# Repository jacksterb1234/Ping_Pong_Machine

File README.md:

# Ping Pong Machine — Table Tennis Serving Robot

A fully custom table tennis serving robot designed for serve-receive practice. Features dual-axis spin control (pitch and yaw), a printed spindexer, and a Bluetooth mobile app for wireless control. Powered entirely from a single USB-C connection.

## Features

- **Dual-axis spin control** — independent pitch and yaw adjustment for realistic serve variation
- **Printed spindexer** — feeds and spins balls for consistent delivery
- **Bluetooth control** via a custom mobile app (Expo/React Native) for easy wireless operation
- **USB-C powered** — single cable for full system power
- **Modular electronics design:**
  - USB-C PD power negotiation board
  - Motor and microcontroller breakout board
  - Buck voltage regulation board
- Designed and fabricated with **JLCPCB** for PCB production

## Repository Structure

```
Ping_Pong_Machine/
├── Kicad/               # KiCad PCB projects (power, motor breakout, buck reg)
├── Code/                # Microcontroller firmware and Bluetooth app code
├── CAD/                 # 3D-printable parts (spindexer, frame, wheels)
├── Sims/                # Simulations for board fit and assembly
└── ul_PTPS543021DRLR/   # Custom KiCad footprint
```

## Electronics

| Board | Function |
|-------|----------|
| USB-C PD board | Negotiates input voltage from USB-C PD source |
| Motor breakout | Drives launch and spin motors |
| MCU breakout | Hosts microcontroller and Bluetooth module |
| Buck regulator | Steps down voltage for logic-level components |

## Mobile App

Controlled via a custom **React Native (Expo)** app that connects over Bluetooth. The app allows users to adjust spin type, speed, and frequency from their phone—no physical controls on the machine required.

## Tools Used

- **KiCad** — PCB schematic and layout
- **JLCPCB** — PCB fabrication and SMT assembly
- **Fusion360 / SolidWorks** — Mechanical CAD (frame and launcher)
- **Expo (React Native)** — Mobile app development

## Author

**Jackson Barber** — [github.com/jacksterb1234](https://github.com/jacksterb1234)

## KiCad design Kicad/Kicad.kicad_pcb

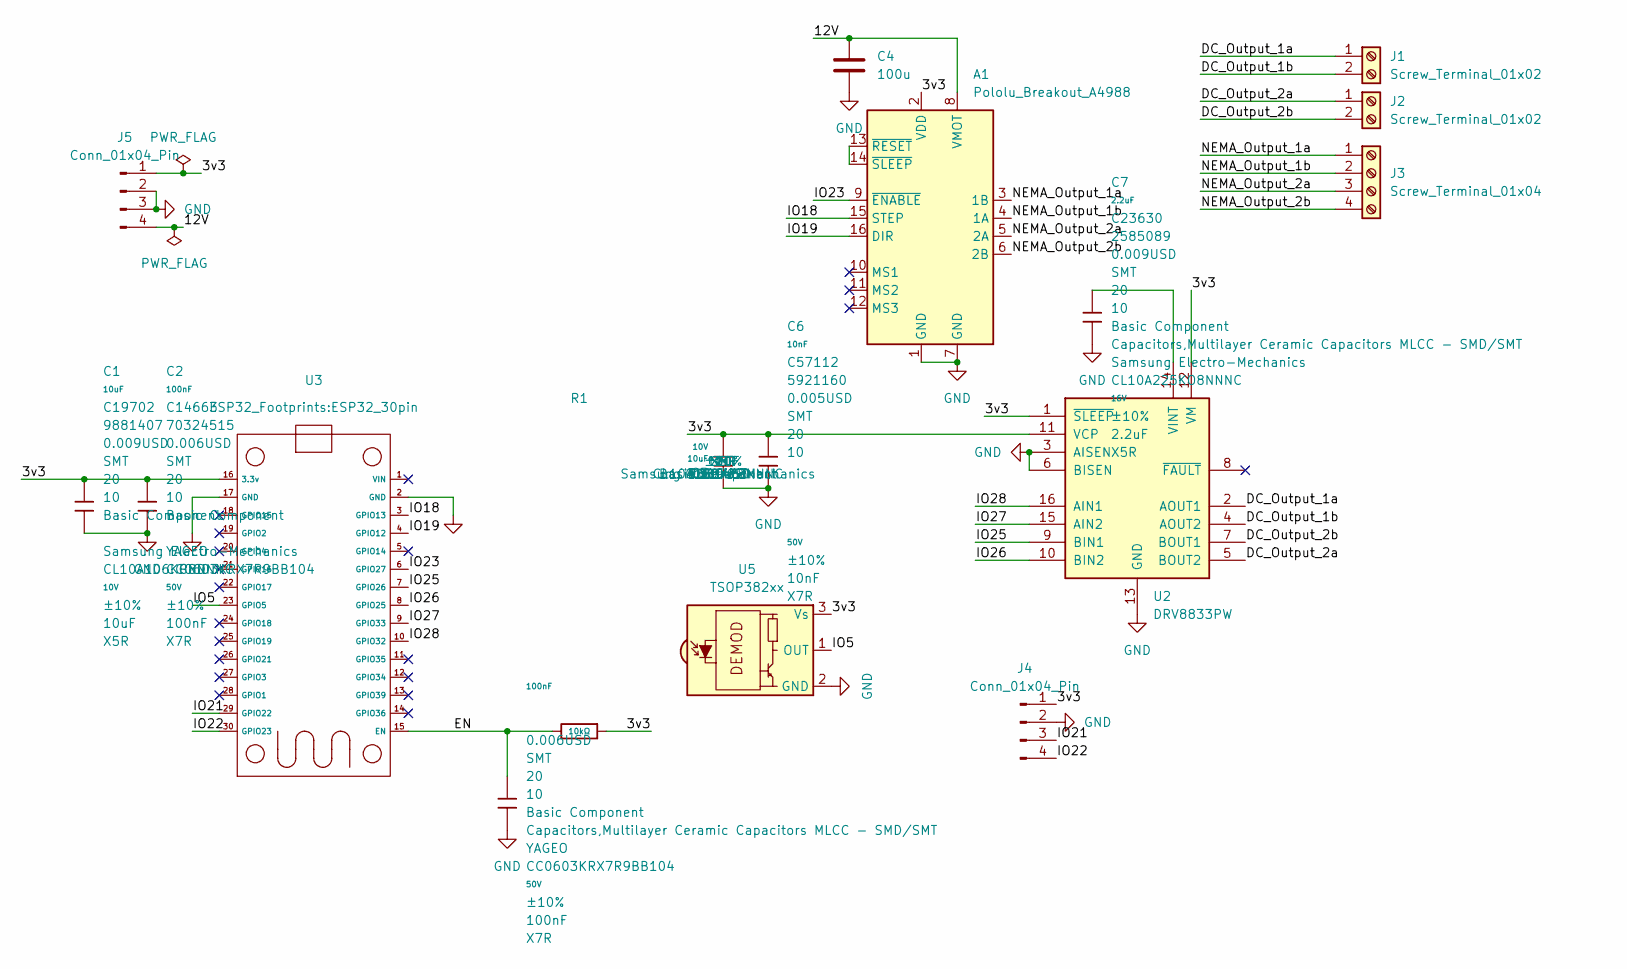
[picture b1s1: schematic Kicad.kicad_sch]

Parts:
A1: Pololu_Breakout_A4988; Pololu_Breakout-16_15.2x20.3mm
C1, C5: 10uF; C_0805_2012Metric_Pad1.18x1.45mm_HandSolder; Voltage Rated 10V; Tolerance ±10%; Part CL10A106KP8NNNC; LCSC C19702
C2, C3: 100nF; C_0805_2012Metric_Pad1.18x1.45mm_HandSolder; Voltage Rated 50V; Tolerance ±10%; Part CC0603KRX7R9BB104; LCSC C14663
C4: 100u; C_Radial_D8.0mm_H11.5mm_P3.50mm
C6: 10nF; C_0805_2012Metric_Pad1.18x1.45mm_HandSolder; Voltage Rated 50V; Tolerance ±10%; Part 0603B103K500NT; LCSC C57112
C7: 2.2uF; C_0805_2012Metric_Pad1.18x1.45mm_HandSolder; Voltage Rated 16V; Tolerance ±10%; Part CL10A225KO8NNNC; LCSC C23630
J1, J2: Screw_Terminal_01x02; TerminalBlock_RND_205-00045_1x02_P5.00mm_Horizontal
J3: Screw_Terminal_01x04; TerminalBlock_RND_205-00003_1x04_P5.00mm_Horizontal
J4, J5: Conn_01x04_Pin; PinHeader_1x04_P2.54mm_Vertical
R1: 10kΩ; R_0805_2012Metric_Pad1.20x1.40mm_HandSolder; Overload Voltage (Max) 75V; Tolerance ±1%; Part 0603WAF1002T5E; LCSC C25804
U2: DRV8833PW; TSSOP-16_4.4x5mm_P0.65mm
U3: ESP32_30pin
U5: TSOP382xx; Vishay_MINICAST-3Pin

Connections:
/3v3: A1.2 (VDD), C1.2, C2.2, C5.2, C6.2, J4.1, J5.1, R1.1, U2.1 (~SLEEP), U2.11 (VCP), U2.12 (VM), U3.16 (3.3v), U5.3 (Vs)
/12V: A1.8 (VMOT), C4.2, J5.4
/DC_Output_1a: J1.1, U2.2 (AOUT1)
/DC_Output_1b: J1.2, U2.4 (AOUT2)
/DC_Output_2a: J2.1, U2.5 (BOUT2)
/DC_Output_2b: J2.2, U2.7 (BOUT1)
/EN: C3.1, R1.2, U3.15 (EN)
/IO5: U3.23 (GPIO5), U5.1 (OUT)
/IO18: A1.15 (STEP), U3.3 (GPIO13)
/IO19: A1.16 (DIR), U3.4 (GPIO12)
/IO21: J4.3, U3.29 (GPIO22)
/IO22: J4.4, U3.30 (GPIO23)
/IO23: A1.9 (~ENABLE), U3.6 (GPIO27)
/IO25: U2.9 (BIN1), U3.7 (GPIO26)
/IO26: U2.10 (BIN2), U3.8 (GPIO25)
/IO27: U2.15 (AIN2), U3.9 (GPIO33)
/IO28: U2.16 (AIN1), U3.10 (GPIO32)
/NEMA_Output_1a: A1.3 (1B), J3.1
/NEMA_Output_1b: A1.4 (1A), J3.2
/NEMA_Output_2a: A1.5 (2A), J3.3
/NEMA_Output_2b: A1.6 (2B), J3.4
GND: A1.1 (GND), A1.7 (GND), C1.1, C2.1, C3.2, C4.1, C5.1, C6.1, C7.1, J4.2, J5.2, J5.3, U2.3 (AISEN), U2.6 (BISEN), U2.13 (GND), U3.2 (GND), U3.17 (GND), U5.2 (GND)
unnamed: A1.13 (~RESET), A1.14 (~SLEEP)
unnamed: C7.2, U2.14 (VINT)

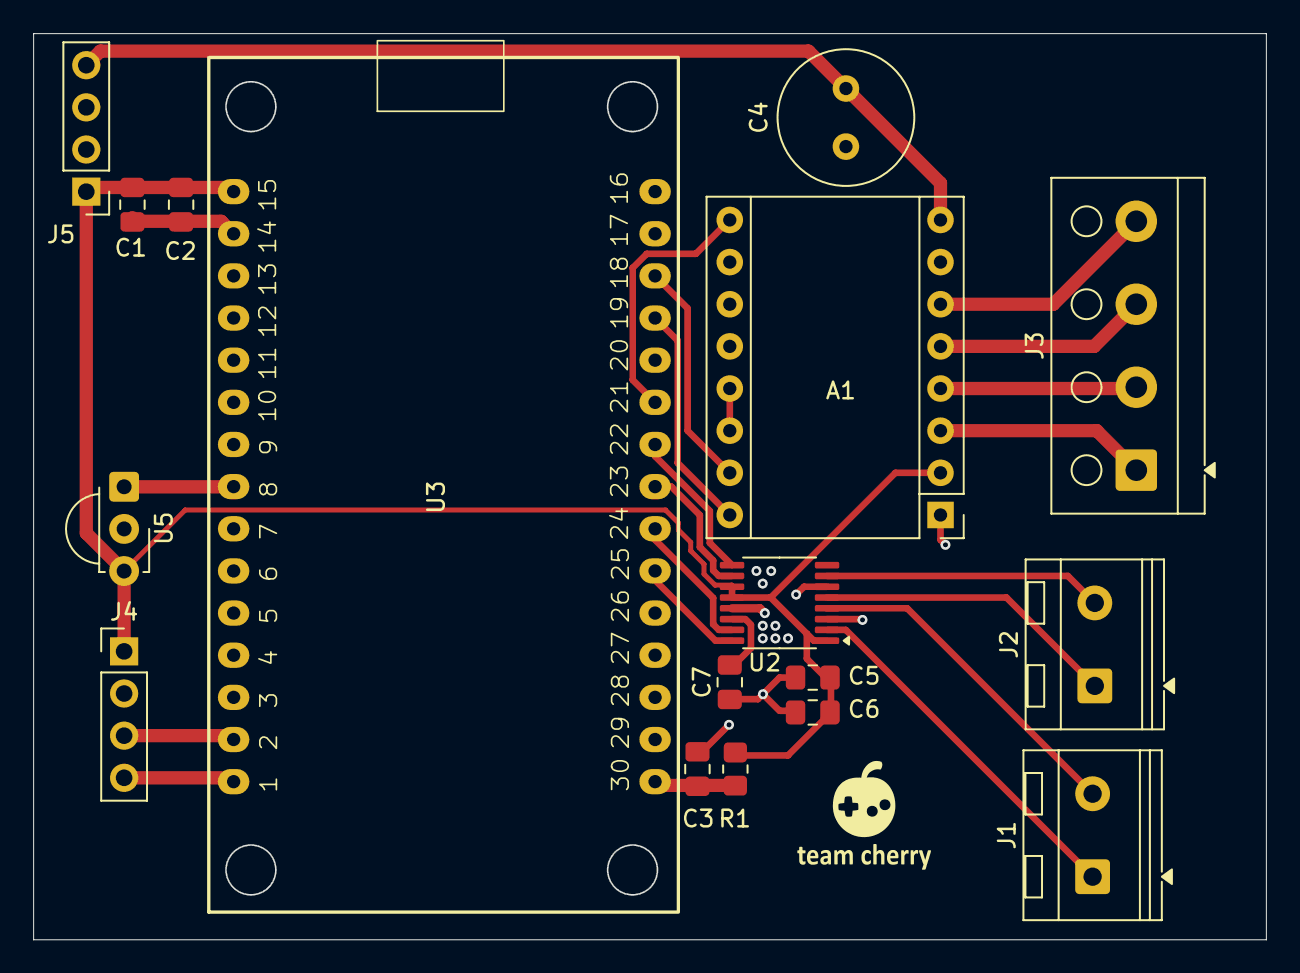
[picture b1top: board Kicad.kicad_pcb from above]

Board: 2 copper layers, 74.3 x 54.6 mm, 17 parts (0 on the bottom side), 24 nets.

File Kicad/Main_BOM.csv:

"Id";"Designator";"Footprint";"Quantity";"Designation";"Supplier and ref";
1;"U5";"Vishay_MINICAST-3Pin";1;"TSOP382xx";;;
2;"C2,C3";"C_0603_1608Metric";2;"0.1u";;;
3;"R1";"R_0603_1608Metric";1;"10k";;;
4;"U3";"ESP32_30pin";1;"~";;;
5;"C5,C1";"C_0603_1608Metric";2;"10u";;;
6;"A1";"Pololu_Breakout-16_15.2x20.3mm";1;"Pololu_Breakout_A4988";;;
7;"C4";"C_0603_1608Metric";1;"100u";;;
8;"C7";"C_0603_1608Metric";1;"2.2u";;;
9;"J4,J5";"PinHeader_1x04_P2.54mm_Vertical";2;"Conn_01x04_Pin";;;
10;"C6";"C_0603_1608Metric";1;"0.01u";;;
11;"J2,J1";"TerminalBlock_RND_205-00232_1x02_P5.08mm_Horizontal";2;"Screw_Terminal_01x02";;;
12;"U2";"TSSOP-16_4.4x5mm_P0.65mm";1;"DRV8833PW";;;
13;"J3";"TerminalBlock_Phoenix_MKDS-3-4-5.08_1x04_P5.08mm_Horizontal";1;"Screw_Terminal_01x04";;;

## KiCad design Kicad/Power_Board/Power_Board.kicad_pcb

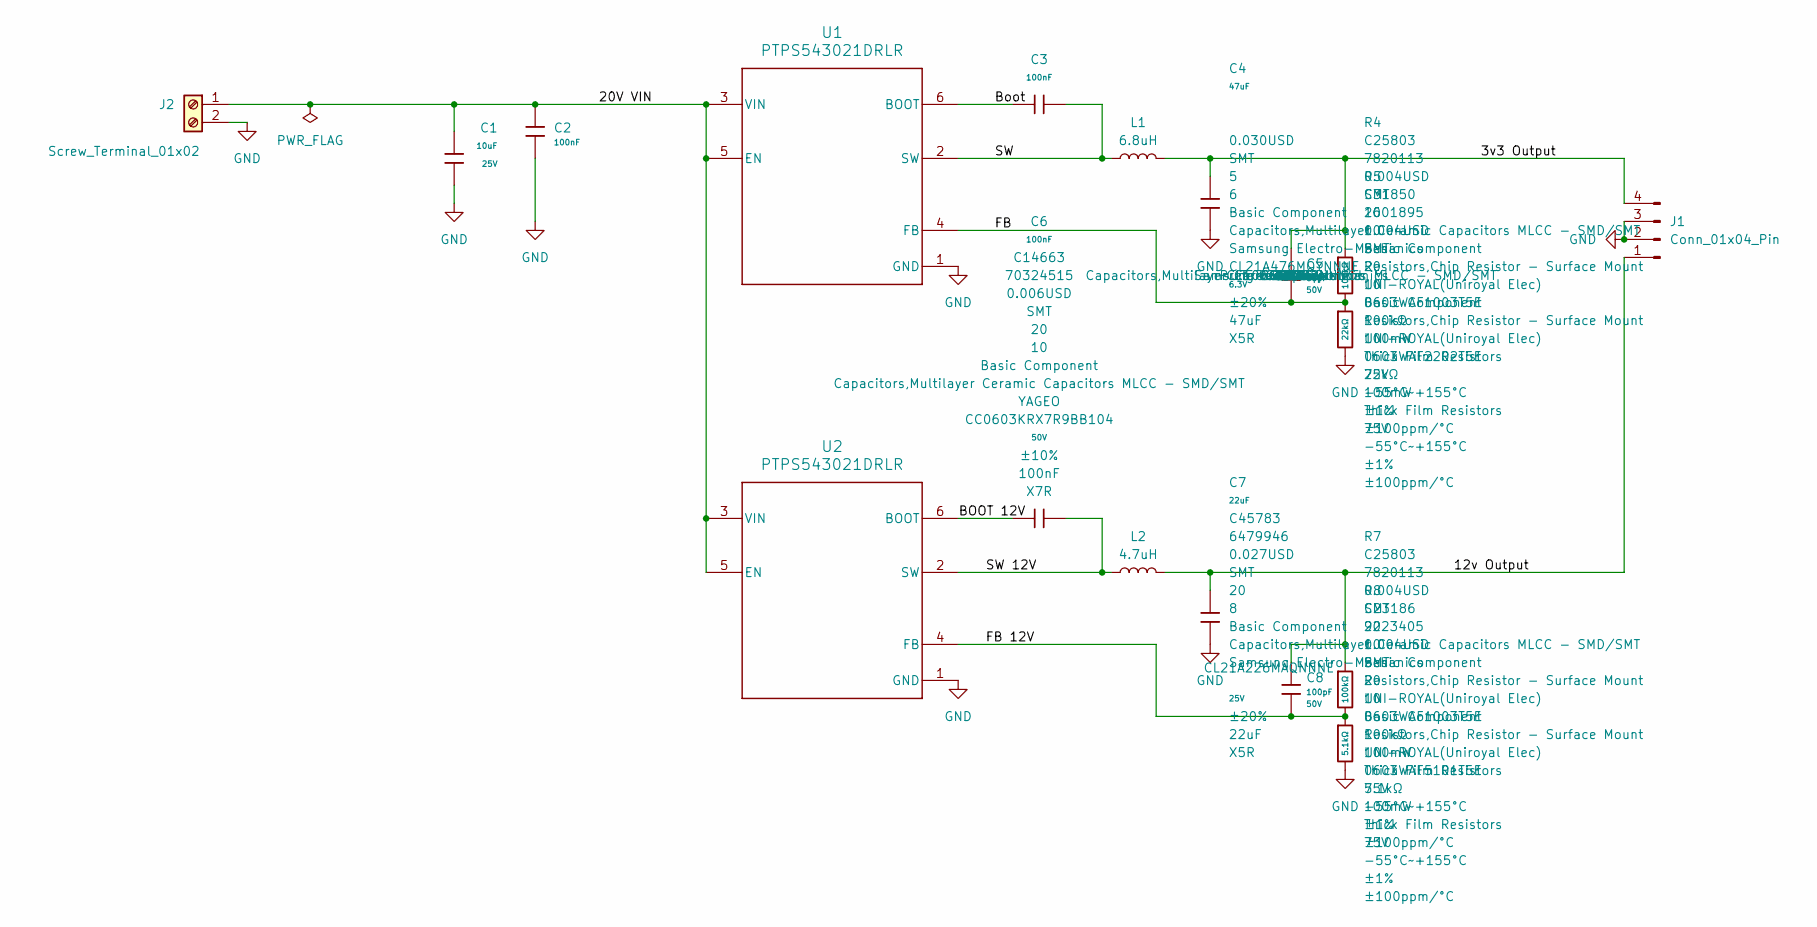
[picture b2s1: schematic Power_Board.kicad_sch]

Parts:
C1: 10uF; C_0805_2012Metric_Pad1.18x1.45mm_HandSolder; Voltage Rated 25V; Tolerance ±20%; Part CL10A106MA8NRNC; LCSC C96446
C2, C3, C6: 100nF; C_0805_2012Metric_Pad1.18x1.45mm_HandSolder; Voltage Rated 50V; Tolerance ±10%; Part CC0603KRX7R9BB104; LCSC C14663
C4: 47uF; C_0805_2012Metric_Pad1.18x1.45mm_HandSolder; Voltage Rated 6.3V; Tolerance ±20%; Part CL21A476MQYNNNE; LCSC C16780
C5: 68pF; C_0805_2012Metric_Pad1.18x1.45mm_HandSolder; Voltage Rated 50V; Tolerance ±5%; Part CL10C680JB8NNNC; LCSC C28262
C7: 22uF; C_0805_2012Metric_Pad1.18x1.45mm_HandSolder; Voltage Rated 25V; Tolerance ±20%; Part CL21A226MAQNNNE; LCSC C45783
C8: 100pF; C_0805_2012Metric_Pad1.18x1.45mm_HandSolder; Voltage Rated 50V; Tolerance ±5%; Part CL10C101JB8NNNC; LCSC C14858
J1: Conn_01x04_Pin; PinSocket_1x04_P2.54mm_Vertical
J2: Screw_Terminal_01x02; TerminalBlock_RND_205-00045_1x02_P5.00mm_Horizontal
L1: 6.8uH; L_TDK_VLS6045EX_VLS6045AF
L2: 4.7uH; L_TDK_VLS6045EX_VLS6045AF
R4, R7: 100kΩ; R_0805_2012Metric_Pad1.20x1.40mm_HandSolder; Overload Voltage (Max) 75V; Tolerance ±1%; Part 0603WAF1003T5E; LCSC C25803
R5: 22kΩ; R_0805_2012Metric_Pad1.20x1.40mm_HandSolder; Overload Voltage (Max) 75V; Tolerance ±1%; Part 0603WAF2202T5E; LCSC C31850
R8: 5.1kΩ; R_0805_2012Metric_Pad1.20x1.40mm_HandSolder; Overload Voltage (Max) 75V; Tolerance ±1%; Part 0603WAF5101T5E; LCSC C23186
U1, U2: PTPS543021DRLR; DRL0006A-MFG

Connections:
/3v3 Output: C4.1, C5.1, J1.4, L1.2, R4.1
/12v Output: C7.1, C8.1, J1.1, L2.2, R7.1
/20V VIN: C1.1, C2.1, J2.1, U1.3 (VIN), U1.5 (EN), U2.3 (VIN), U2.5 (EN)
/BOOT 12V: C6.1, U2.6 (BOOT)
/Boot: C3.1, U1.6 (BOOT)
/FB: C5.2, R4.2, R5.1, U1.4 (FB)
/FB 12V: C8.2, R7.2, R8.1, U2.4 (FB)
/SW: C3.2, L1.1, U1.2 (SW)
/SW 12V: C6.2, L2.1, U2.2 (SW)
GND: C1.2, C2.2, C4.2, C7.2, J1.2, J1.3, J2.2, R5.2, R8.2, U1.1 (GND), U2.1 (GND)

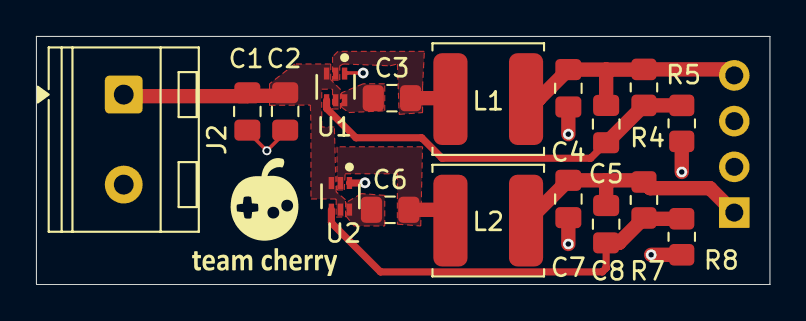
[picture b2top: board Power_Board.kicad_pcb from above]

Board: 2 copper layers, 40.8 x 13.8 mm, 18 parts (1 on the bottom side), 10 nets.

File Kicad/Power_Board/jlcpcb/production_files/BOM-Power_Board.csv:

Comment,Designator,Footprint,LCSC,Quantity
100kΩ,"R4,R7",R_0805_2012Metric_Pad1.20x1.40mm_HandSolder,C25803,2
100nF,"C2,C3,C6",C_0805_2012Metric_Pad1.18x1.45mm_HandSolder,C14663,3
100pF,C8,C_0805_2012Metric_Pad1.18x1.45mm_HandSolder,C14858,1
10uF,C1,C_0805_2012Metric_Pad1.18x1.45mm_HandSolder,C96446,1
22kΩ,R5,R_0805_2012Metric_Pad1.20x1.40mm_HandSolder,C31850,1
22uF,C7,C_0805_2012Metric_Pad1.18x1.45mm_HandSolder,C45783,1
47uF,C4,C_0805_2012Metric_Pad1.18x1.45mm_HandSolder,C16780,1
5.1kΩ,R8,R_0805_2012Metric_Pad1.20x1.40mm_HandSolder,C23186,1
68pF,C5,C_0805_2012Metric_Pad1.18x1.45mm_HandSolder,C28262,1
6.8uH,L1,L_TDK_VLS6045EX_VLS6045AF,,1
PTPS543021DRLR,U2,DRL0006A-MFG,,1
Screw_Terminal_01x02,J2,TerminalBlock_RND_205-00045_1x02_P5.00mm_Horizontal,,1
4.7uH,L2,L_TDK_VLS6045EX_VLS6045AF,,1
Conn_01x04_Pin,J1,PinSocket_1x04_P2.54mm_Vertical,,1
PTPS543021DRLR,U1,DRL0006A-MFG,,1

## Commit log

2026-01-09 Updated File Structure
2026-01-10 Added Power Board
2026-01-11 Updated schematic for main board
2026-01-12 Main Board v1
2026-01-14 Created cad for how the boards will fit together
2026-01-18 Wrote v1 of the code, final version of boards
2026-01-19 Updated to use 0805 instead of JLC assembly
2026-02-01 Created expo app and updated code
2026-02-07 Modified Motor Mounting
2026-03-04 Updated Power Board
2026-05-30 Add README
    Added detailed project description, features, repository structure, electronics overview, mobile app functionality, tools used, and author information.
